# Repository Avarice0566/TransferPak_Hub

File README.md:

# TransferPakHub

This repository provides a standalone Transfer Pak hub PCB designed to fit inside an N64 DexDrive case.  

## Requirements
- Transplant all surface-mount and DIP components from an **N64 controller PCB** (model: `CFS8120-200010-00`).  
- Optionally, add a **1.8mm LED** with the appropriate resistor to utilize the DexDrive case’s LED diffuser.
- Digikey Part No. SW1139-ND can be used to plug the DC jack hole in the dexdrive case

## Notes
- All DIP components are mounted on the opposite side of the board for clearance.  
- **Use at your own risk.** I am not responsible for any damage to your N64, its accessories, or your Game Boy cartridges.  

- Bottom label. Replaces Interact DEXDRIVE label with something that looks more akin to a real Nintendo product. (The label needs to be 26mm in height and 35mm in width)

Special thanks to Modman(RWeick), Bigbass, and everyone on the N64BREW Discord.

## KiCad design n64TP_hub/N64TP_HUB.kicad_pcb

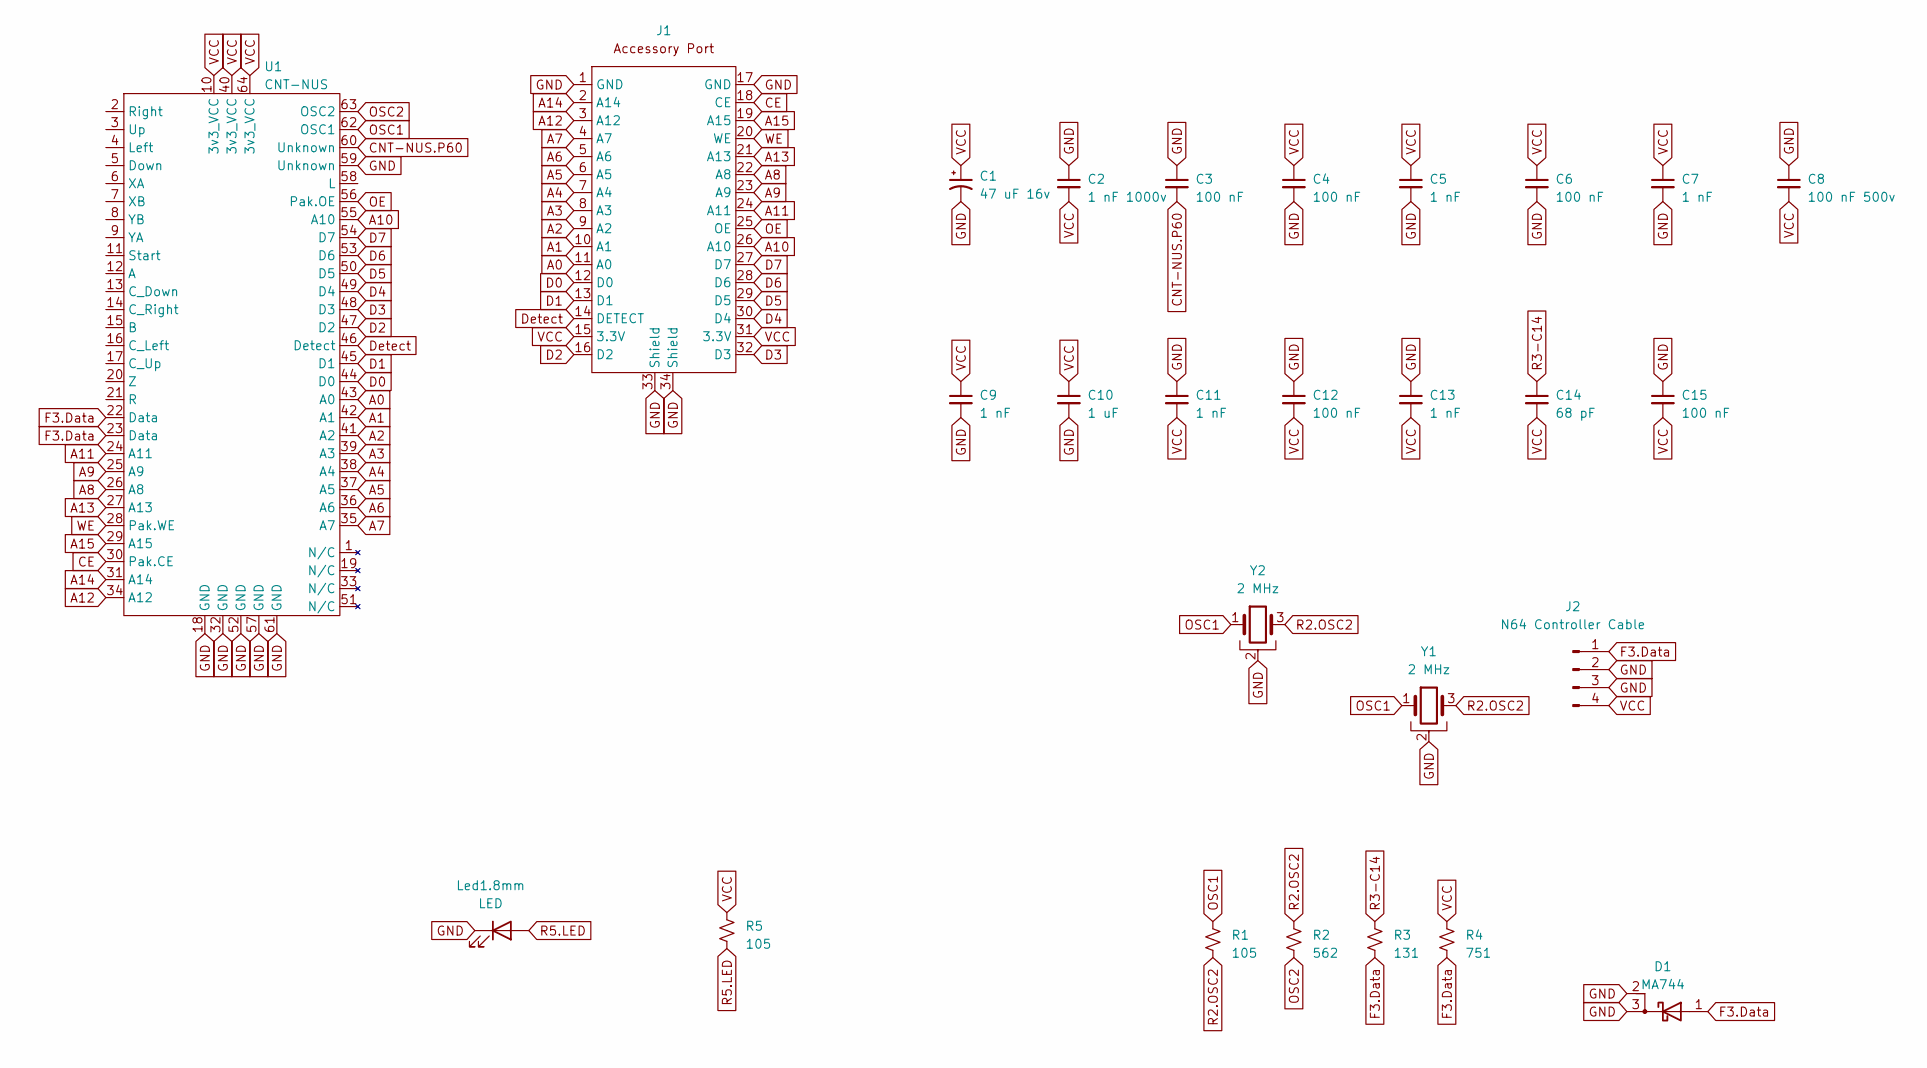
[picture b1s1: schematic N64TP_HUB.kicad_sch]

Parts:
C1: 47 uF 16v; CP_Radial_D5.0mm_P2.50mm
C2: 1 nF 1000v; TH Capacitor
C3, C4, C6, C12, C15: 100 nF; Small SMD
C5, C7, C9, C11, C13: 1 nF; Small SMD
C8: 100 nF 500v; TH Capacitor
C10: 1 uF; Small SMD
C14: 68 pF; Small SMD
D1: MA744; SOT-23 Diode
J1: Accessory Port
J2: N64 Controller Cable; N64 Plug Cable Connector
Led1.8mm: LED
R1, R5: 105; Large SMD
R2: 562; Large SMD
R3: 131; Small SMD
R4: 751; Small SMD
U1: CNT-NUS
Y1: 2 MHz; 2 MHz Oscillator
Y2: 2 MHz; 2 Mhz Oscillator SMD

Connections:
A: U1.12 (A)
A0: J1.11 (A0), U1.43 (A0)
A1: J1.10 (A1), U1.42 (A1)
A2: J1.9 (A2), U1.41 (A2)
A3: J1.8 (A3), U1.39 (A3)
A4: J1.7 (A4), U1.38 (A4)
A5: J1.6 (A5), U1.37 (A5)
A6: J1.5 (A6), U1.36 (A6)
A7: J1.4 (A7), U1.35 (A7)
A8: J1.22 (A8), U1.26 (A8)
A9: J1.23 (A9), U1.25 (A9)
A10: J1.26 (A10), U1.55 (A10)
A11: J1.24 (A11), U1.24 (A11)
A12: J1.3 (A12), U1.34 (A12)
A13: J1.21 (A13), U1.27 (A13)
A14: J1.2 (A14), U1.31 (A14)
A15: J1.19 (A15), U1.29 (A15)
B: U1.15 (B)
CD: U1.13 (C_Down)
CE: J1.18 (CE), U1.30 (Pak.CE)
CL: U1.16 (C_Left)
CNT-NUS.P60: C3.2, U1.60 (Unknown)
CR: U1.14 (C_Right)
CU: U1.17 (C_Up)
D0: J1.12 (D0), U1.44 (D0)
D1: J1.13 (D1), U1.45 (D1)
D2: J1.16 (D2), U1.47 (D2)
D3: J1.32 (D3), U1.48 (D3)
D4: J1.30 (D4), U1.49 (D4)
D5: J1.29 (D5), U1.50 (D5), U1.51 (D5)
D6: J1.28 (D6), U1.53 (D6)
D7: J1.27 (D7), U1.54 (D7)
Detect: J1.14 (DETECT), U1.46 (Detect)
Down: U1.5 (Down)
F3.Data: D1.1 (A), J2.1, R3.2, R4.2, U1.22 (Data), U1.23 (Data)
GND: C1.2, C2.1, C3.1, C4.2, C5.2, C6.2, C7.2, C8.1, C9.2, C10.2, C11.1, C12.1, C13.1, C15.1, D1.2 (K), D1.3 (K), J1.1 (GND), J1.17 (GND), J1.33 (Shield), J1.34 (Shield), J2.2, J2.3, Led1.8mm.1 (K), U1.18 (GND), U1.19 (Unknown), U1.32 (GND), U1.52 (GND), U1.57 (GND), U1.59 (Unknown), U1.61 (GND), Y1.2, Y2.2; also elsewhere on the board
L: U1.58 (L)
Left: U1.4 (Left)
OE: J1.25 (OE), U1.56 (Pak.OE)
OSC1: R1.1, U1.62 (OSC1), Y1.1, Y2.1
OSC2: R2.2, U1.63 (OSC2)
R: U1.21 (R)
R2.OSC2: R1.2, R2.1, Y1.3, Y2.3
R3-C14: C14.1, R3.1
Right: U1.2 (Right)
Start: U1.11 (Start)
Up: U1.3 (Up)
WE: J1.20 (WE), U1.28 (Pak.WE)
XA: U1.6 (XA)
XB: U1.7 (XB)
YA: U1.9 (YA)
YB: U1.8 (YB)
Z: U1.20 (Z)

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
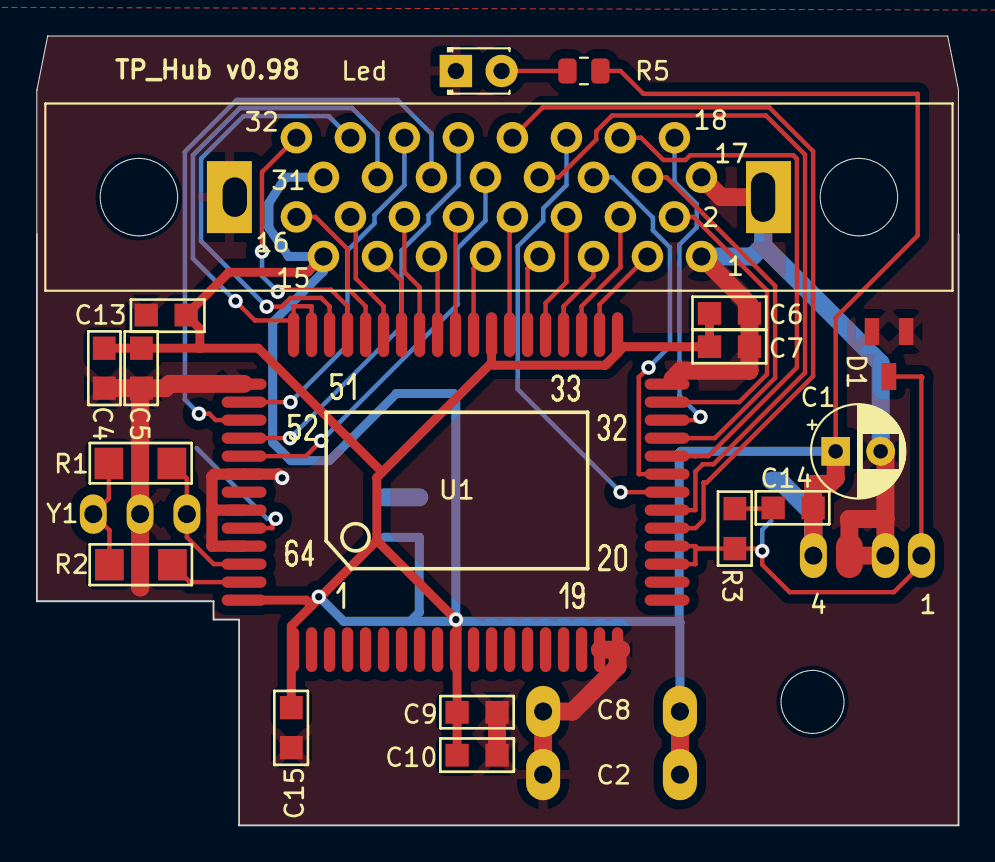
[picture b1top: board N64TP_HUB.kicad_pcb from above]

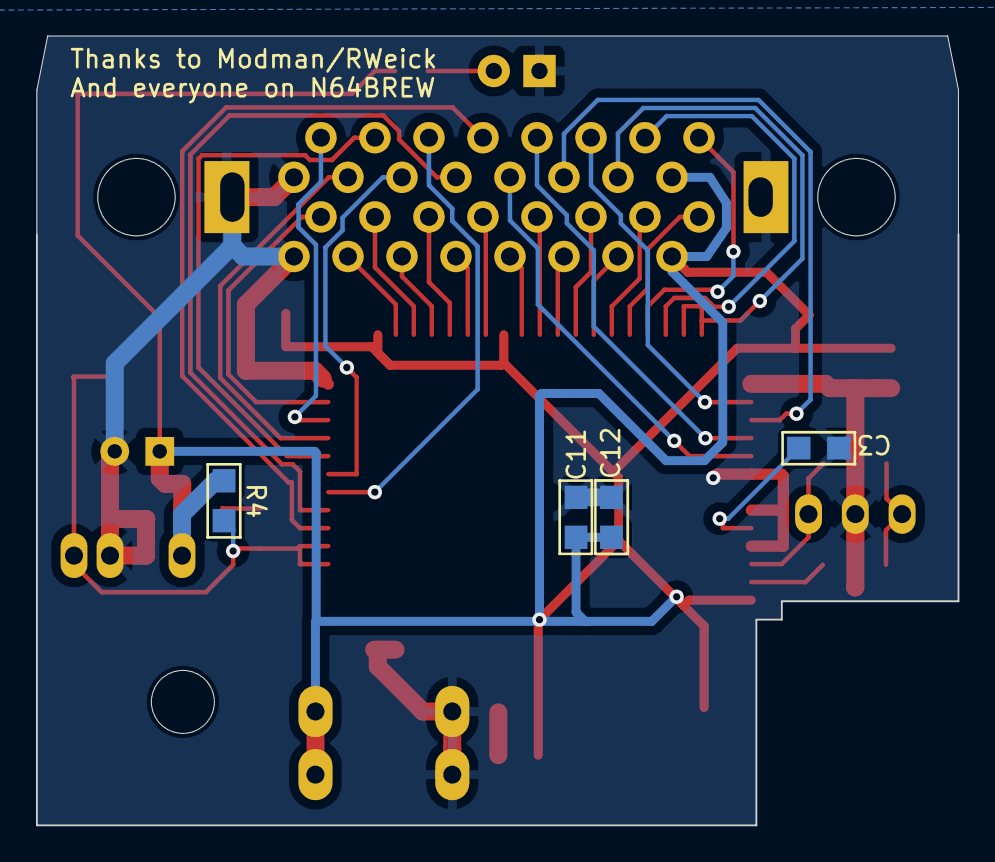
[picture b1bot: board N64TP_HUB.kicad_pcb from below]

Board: 2 copper layers, 51.2 x 43.9 mm, 26 parts (4 on the bottom side), 37 nets.

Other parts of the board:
Led: LED_D1.8mm_W3.3mm_H2.4mm

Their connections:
GND: Led.1; also elsewhere on the board

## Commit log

2025-08-19 Add files via upload
    TP_HUB v0.98
